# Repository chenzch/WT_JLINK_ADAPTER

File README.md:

JLink Adapter to Mini-10. Powered by WTMEC.

<Peter_Chen@wtmec.com>

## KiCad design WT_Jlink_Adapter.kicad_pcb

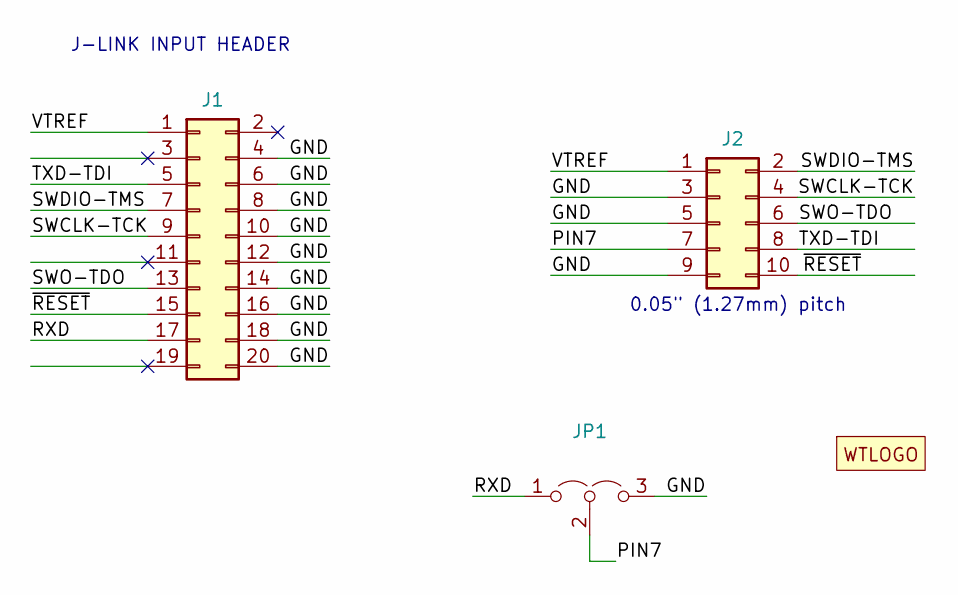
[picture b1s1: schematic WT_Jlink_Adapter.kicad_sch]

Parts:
J1: Conn_02x10_Odd_Even; PinSocket_2x10_P2.54mm_Horizontal
J2: Conn_02x05_Odd_Even; PinHeader_2x05_P1.27mm_Vertical
JP1: Jumper_3_Open; PinHeader_1x03_P2.54mm_Vertical
LOGO1: WTLogo

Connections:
/GND: J1.4, J1.6, J1.8, J1.10, J1.12, J1.14, J1.16, J1.18, J1.20, J2.3, J2.5, J2.9, JP1.3 (B)
/PIN7: J2.7, JP1.2 (C)
/RXD: J1.17, JP1.1 (A)
/SWCLK-TCK: J1.9, J2.4
/SWDIO-TMS: J1.7, J2.2
/SWO-TDO: J1.13, J2.6
/TXD-TDI: J1.5, J2.8
/VTREF: J1.1, J2.1
/~RESET: J1.15, J2.10

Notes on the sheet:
J-LINK INPUT HEADER
0.05" (1.27mm) pitch

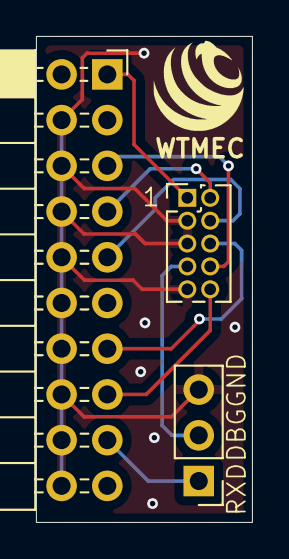
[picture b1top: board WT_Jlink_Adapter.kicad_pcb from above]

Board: 2 copper layers, 12.0 x 27.0 mm, 4 parts (0 on the bottom side), 9 nets.

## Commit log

2024-07-20 Update Layout
2024-07-22 Update pdf
2025-02-22 Update to Kicad 9
